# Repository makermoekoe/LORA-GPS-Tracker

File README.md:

# LORA-GPS-Tracker

**This page is a work in progress!**

</a>

This LORA-GPS-Tracker was designed to just test three modules, which I haven't worked with yet: the RFM95 LORA module, the ESP32-S2-Mini module and the ATGM336h GPS module. All combined this device can be used as a GPS-Tracker for LORA based systems. Additionally to the modules, the board includes a 0.96" OLED display, two user buttons, a user RGB LED, a LiPo battery charger with a 16340 cell holder, and a dual LDO setup, which is very handy when it comes to deep sleeping.

Here are some specs of the board:
- ESP32-S2-Mini
- USB Type-C for charging the battery and flashing the ESP32
- Dual LDO setup, which will reduce the sleep current (the main power sinks can be shut down before entering a sleep mode)
- Power friendly OLED display
- Dimensions are 60x43mm

The [Youtube Video](https://youtu.be/C7jFupvuy9M) shows the PCB assembly process, some initial tests and some power measurements.

## Connections

The RFM95 LORA module is connected via SPI, the ATGM336h GPS module is connected via UART and the OLED display is connected via I2C.

GPIO ESP32 | Function | Mode
-------- | -------- | --------
GPIO1 | LORA_RST | Output
GPIO2 | LORA_MISO | Input
GPIO3 | LORA_MOSI | Output
GPIO4 | LORA_SCK | Output
GPIO5 | LORA_CS | Output
GPIO6 | LORA_INT | Input
GPIO7 | LORA_DIO1 | Data
GPIO8 | LORA_DIO2 | Data
GPIO12 | Button2 | Input
GPIO14 | Enable LDO2 | Output
GPIO15 | BAT_ADC | Input
GPIO16 | Button1 | Input
GPIO19 | USB_DN | Data
GPIO20 | USB_DP | Data
GPIO34 | OLED_RST | Output
GPIO35 | I2C_SCL | Output
GPIO36 | I2C_SDA | Data
GPIO37 | LED_CLK | Output
GPIO38 | LED_SDI | Data
GPIO40 | GPS_PPS | Input
GPIO41 | GPS_RXD | Input
GPIO42 | GPS_TXD | Output

By switching off the EN_LDO2 output, the second LDO which powers the GPS as well as LORA module, the onboard LED and the OLED display, will be shut down.

## Power measurements

</a>

State | Avg. current | Peak current
-------- | -------- | --------
Reading sensors | 80mA | 92mA
Transmitting LORA | 135mA | 208mA
Deep sleep | 75µA | 82µA

Note: The schematics in this repo have the I2C pull-up resistors connected to +3V3. It reduces the power consumption if you don't mount these resistors or if you connect them to VDD (controllable via LDO2).

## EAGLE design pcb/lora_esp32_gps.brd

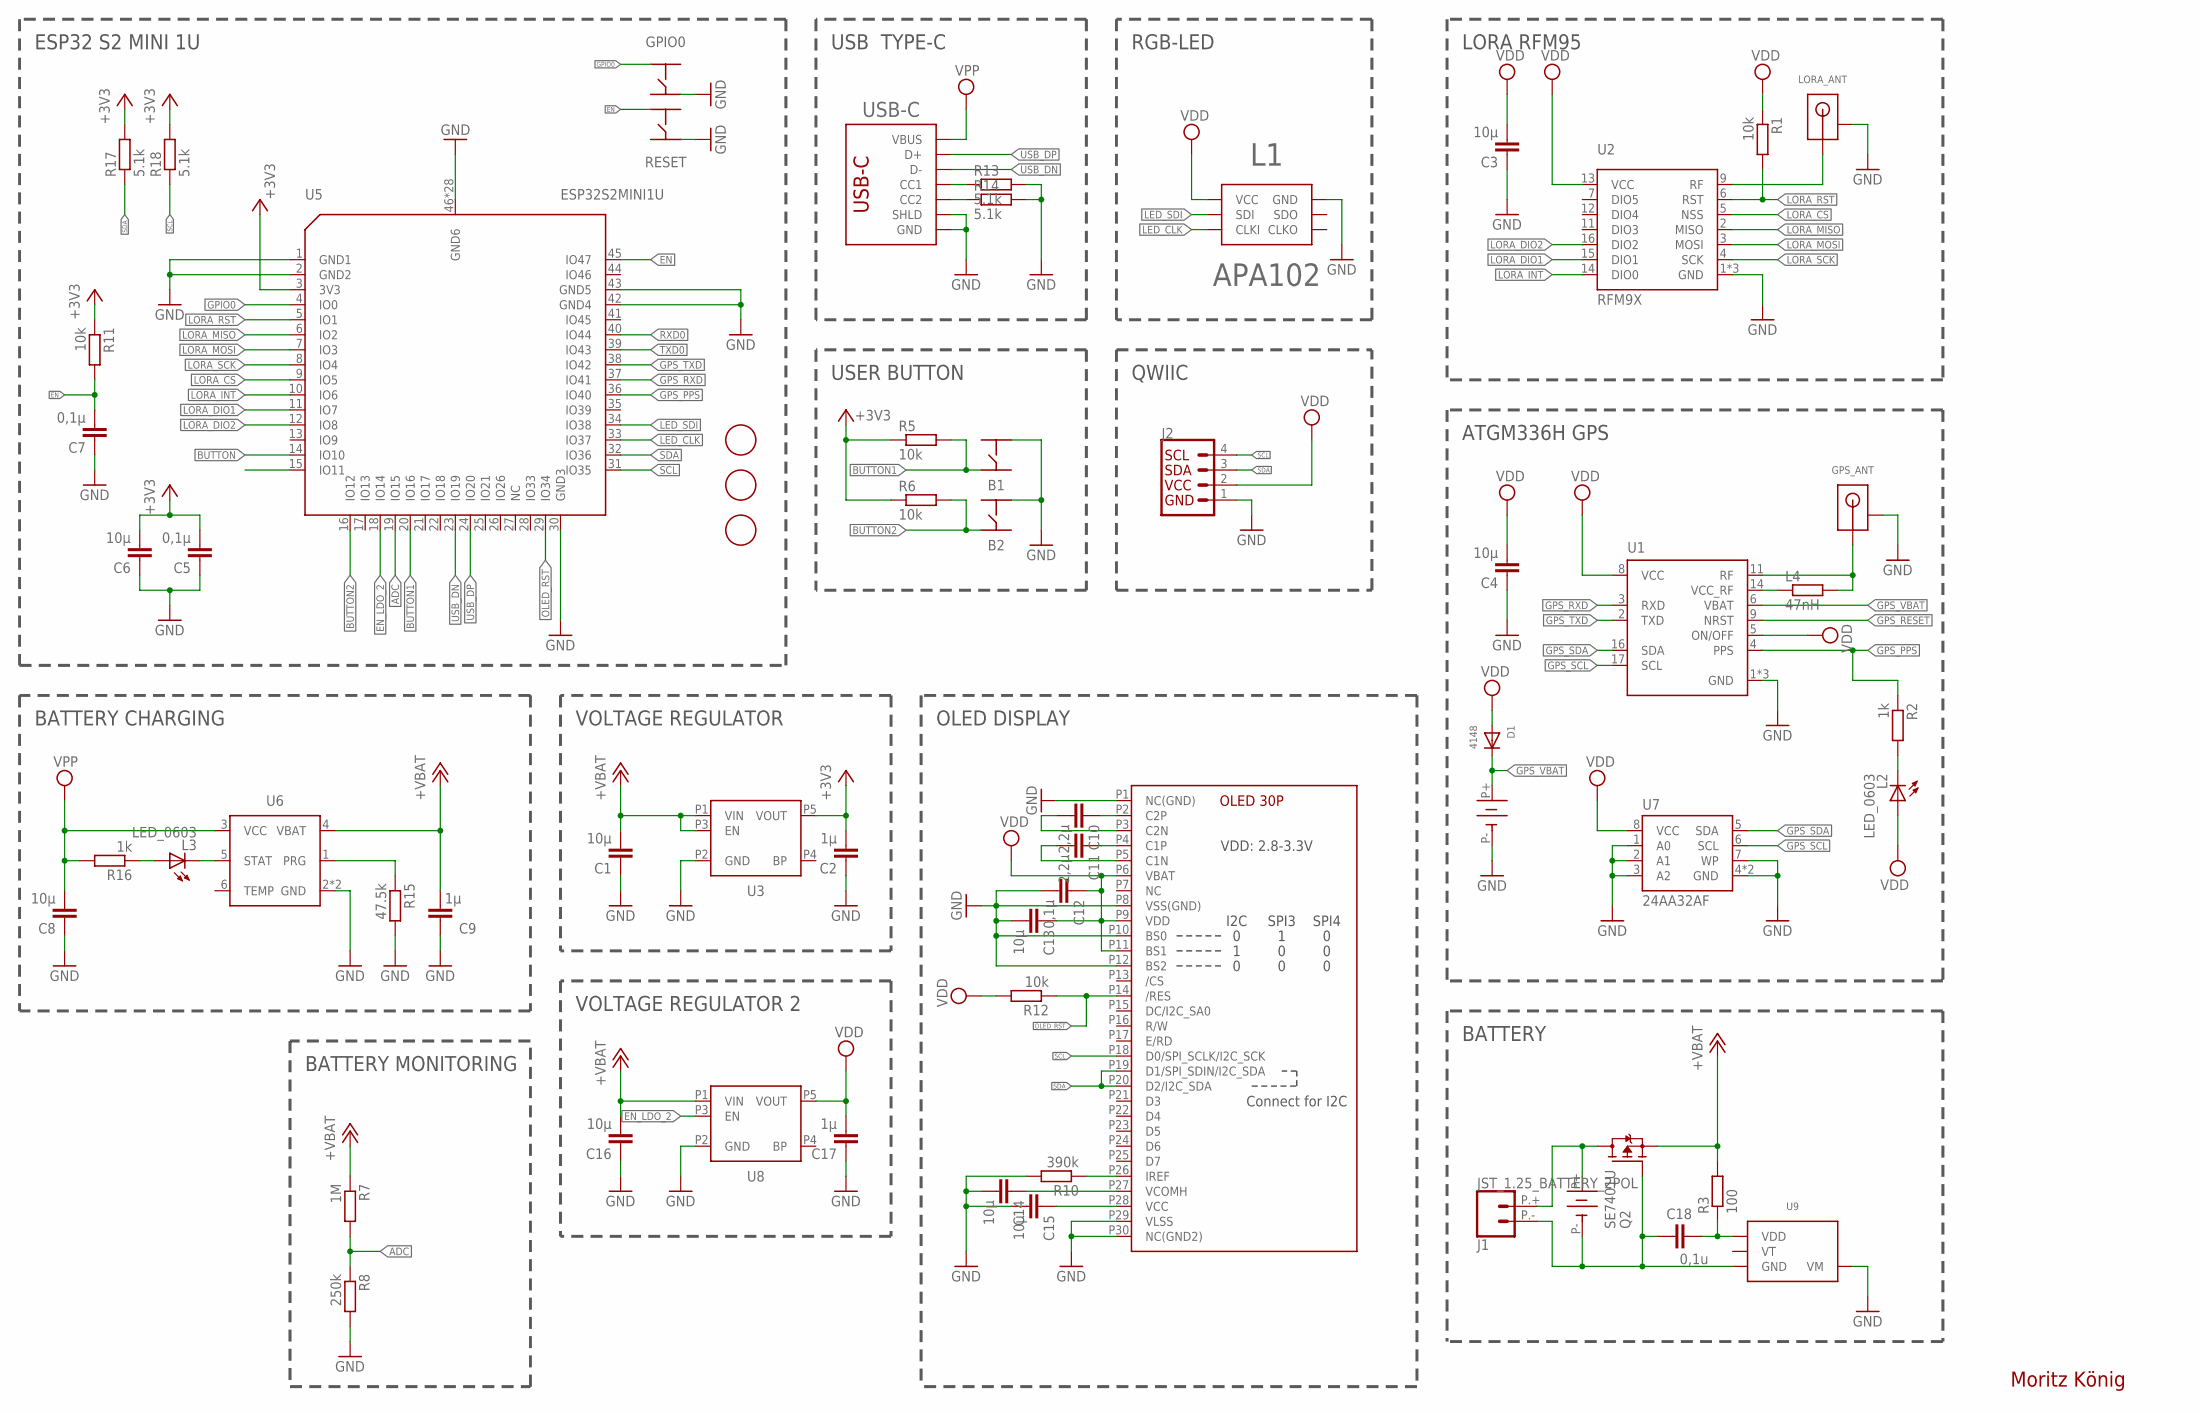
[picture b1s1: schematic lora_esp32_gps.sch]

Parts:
B1, B2: PTS840ESDGMSMTRLFS
BAT2: MS621
C1, C3, C4, C6, C8, C13, C14, C15, C16: 10µ; C0603
C2, C9, C17: 1µ; C0603
C5, C7, C12: 0,1µ; C0603
C10, C11: 2,2µ; C0603
C18: 0,1u; C0603
D1: 4148; SOD-323F
FID1, FID2, FID3: FIDUCIAL; FIDUCIAL_1MM
GPIO0: BUTTON_4PIN_TS_1177; TS-1177-C-B-B
GPS_ANT: UFL_ANT_CONNECTOR
J1: JST_1.25_BATTERY_2POL; JST_1.25MM_2POL
J2: QWIIC_CONNECTORJS-1MM; 1X04_1MM_RA
L1: APA102_2020
L2, L3: LED_0603; CHIPLED_0603
L4: 47nH; R0402
LORA_ANT: UFL_ANT_CONNECTOR
Q2: SE7401U; SOT323
R1, R5, R6, R11, R12: 10k; R0603
R2, R16: 1k; R0603
R3: 100; R0603
R7: 1M; R0603
R8: 250k; R0603
R10: 390k; R0603
R13, R14, R17, R18: 5.1k; R0603
R15: 47.5k; R0603
RESET: BUTTON_4PIN_TS_1177; TS-1177-C-B-B
U1: ATGM336H; ATGM336H-MODULE
U2: RFM9X; LORA_RFM9X
U3, U8: RT9193_SC70-5; SC-70-5
U4: OLD_096_SSD1306_30P_2B; OLED_096_30P_B
U5: ESP32S2MINI1U; ESP32-S2-MINI-1U
U6: WS4518D; DFN-6
U7: 24AA32AF; TDFN8
U9: XB5353A; SOT23-5
U$2: BATTERY_KEYSTONE_1051; KEYSTONE_1051
USB-C: USB_C_C393939; USBC_C393939

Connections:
+3V3: C2.2, C5.2, C6.2, R5.1, R6.1, R11.1, R17.2, R18.2, U3.P5 (VOUT), U5.3 (3V3)
+VBAT: C1.2, C9.2, C16.2, Q2.2 (S), R3.2, R7.1, U3.P1 (VIN), U3.P3 (EN), U6.4 (VBAT), U8.P1 (VIN)
ADC: R7.2, R8.1, U5.19 (IO15)
BUTTON: U5.14 (IO10)
BUTTON1: B1.2, R5.2, U5.20 (IO16)
BUTTON2: B2.2, R6.2, U5.16 (IO12)
EN: C7.2, R11.2, RESET.P4 (4), U5.45 (IO47)
EN_LDO_2: U5.18 (IO14), U8.P3 (EN)
GND: B1.3, B2.3, BAT2.P- (GND), C1.1, C2.1, C3.1, C4.1, C5.1, C6.1, C7.1, C8.1, C9.1, C12.2, C13.2, C14.2, C15.2, C16.1, C17.1, GPIO0.P1 (1), GPS_ANT.P1.- (GND), GPS_ANT.P2.- (GND), J2.1 (GND), L1.P6 (GND), L1.P6.1 (GND), LORA_ANT.P1.- (GND), LORA_ANT.P2.- (GND), R8.2, R10.2, R13.2, R14.2, R15.2, RESET.P1 (1), U1.1 (GND), U1.10 (GND), U1.12 (GND), U2.1 (GND), U2.8 (GND), U2.10 (GND), U3.P2 (GND), U4.P1 (NC(GND)), U4.P8 (VSS(GND)), U4.P10 (BS0), U4.P12 (BS2), U4.P29 (VLSS), U4.P30 (NC(GND2)), U5.1 (GND1), U5.2 (GND2), U5.30 (GND3), U5.42 (GND4), U5.43 (GND5), U5.46 (GND6), U5.47 (GND6), U5.48 (GND6), U5.49 (GND6), U5.50 (GND6), U5.51 (GND6), U5.52 (GND6), U5.53 (GND6), U5.54 (GND6), U5.55 (GND6), U5.56 (GND6), U5.57 (GND6), U5.58 (GND6), U5.59 (GND6), U5.60 (GND6), U5.61 (GND6), U5.62 (GND6), U5.63 (GND6), U5.64 (GND6), U5.65 (GND6), U5.66 (GND6), U5.67 (GND6), U5.68 (GND6), U5.69 (GND6), U5.70 (GND6), U5.71 (GND6), U5.72 (GND6), U5.73 (GND6), U6.2 (GND), U6.EXP (GND), U7.1 (A0), U7.2 (A1), U7.3 (A2), U7.4 (GND), U7.7 (WP), U7.EXP (GND), U8.P2 (GND), U9.4 (VM), U9.5 (VM), USB-C.A1B12 (GND), USB-C.B1A12 (GND), USB-C.S1 (SHLD), USB-C.S2 (SHLD), USB-C.S3 (SHLD), USB-C.S4 (SHLD)
GPIO0: GPIO0.P4 (4), U5.4 (IO0)
GPS_PPS: R2.1, U1.4 (PPS), U5.36 (IO40)
GPS_RESET: U1.9 (NRST)
GPS_RXD: U1.3 (RXD), U5.37 (IO41)
GPS_SCL: U1.17 (SCL), U7.6 (SCL)
GPS_SDA: U1.16 (SDA), U7.5 (SDA)
GPS_TXD: U1.2 (TXD), U5.38 (IO42)
GPS_VBAT: BAT2.P+ (VCC), D1.C, U1.6 (VBAT)
LED_CLK: L1.P5 (CLKI), U5.33 (IO37)
LED_SDI: L1.P4 (SDI), U5.34 (IO38)
LORA_CS: U2.5 (NSS), U5.9 (IO5)
LORA_DIO1: U2.15 (DIO1), U5.11 (IO7)
LORA_DIO2: U2.16 (DIO2), U5.12 (IO8)
LORA_INT: U2.14 (DIO0), U5.10 (IO6)
LORA_MISO: U2.2 (MISO), U5.6 (IO2)
LORA_MOSI: U2.3 (MOSI), U5.7 (IO3)
LORA_RST: R1.2, U2.6 (RST), U5.5 (IO1)
LORA_SCK: U2.4 (SCK), U5.8 (IO4)
unnamed: L4.1, U1.14 (VCC_RF)
unnamed: L2.P$1 (C), R2.2
unnamed: GPS_ANT.ANT, L4.2, U1.11 (RF)
unnamed: LORA_ANT.ANT, U2.9 (RF)
unnamed: C18.2, R3.1, U9.3 (VDD)
unnamed: C18.1, J1.P.- (2), Q2.1 (G), U9.2 (GND), U$2.P- (GND)
unnamed: R15.1, U6.1 (PRG)
unnamed: J1.P.+ (1), Q2.3 (D), U$2.P+ (VCC)
unnamed: R14.1, USB-C.B5 (CC2)
unnamed: C10.1, U4.P2 (C2P)
unnamed: C10.2, U4.P3 (C2N)
unnamed: C11.2, U4.P5 (C1N)
unnamed: R10.1, U4.P26 (IREF)
unnamed: R13.1, USB-C.A5 (CC1)
unnamed: C11.1, U4.P4 (C1P)
unnamed: C15.1, U4.P28 (VCC)
unnamed: C14.1, U4.P27 (VCOMH)
unnamed: L3.P$2 (A), R16.1
unnamed: L3.P$1 (C), U6.5 (STAT)
OLED_RST: R12.1, U4.P14 (/RES), U5.29 (IO34)
RXD0: U5.40 (IO44)
SCL: J2.4 (SCL), R18.1, U4.P18 (D0/SPI_SCLK/I2C_SCK), U5.31 (IO35)
SDA: J2.3 (SDA), R17.1, U4.P19 (D1/SPI_SDIN/I2C_SDA), U4.P20 (D2/I2C_SDA), U5.32 (IO36)
TXD0: U5.39 (IO43)
USB_DN: U5.23 (IO19), USB-C.A7 (D-), USB-C.B7 (D-)
USB_DP: U5.24 (IO20), USB-C.A6 (D+), USB-C.B6 (D+)
VDD: C3.2, C4.2, C12.1, C13.1, C17.2, D1.A, J2.2 (VCC), L1.P1 (VCC), L1.P1.1 (VCC), L2.P$2 (A), R1.1, R12.2, U1.5 (ON/OFF), U1.8 (VCC), U2.13 (VCC), U4.P6 (VBAT), U4.P9 (VDD), U4.P11 (BS1), U7.8 (VCC), U8.P5 (VOUT)
VPP: C8.2, R16.2, U6.3 (VCC), USB-C.A4B9 (VBUS), USB-C.B4A9 (VBUS)

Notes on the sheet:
Moritz König
BATTERY MONITORING
USB TYPE-C
VOLTAGE REGULATOR
RGB-LED
BATTERY CHARGING
BATTERY
USER BUTTON
OLED DISPLAY
QWIIC
ESP32 S2 MINI 1U
LORA RFM95
ATGM336H GPS
VOLTAGE REGULATOR 2

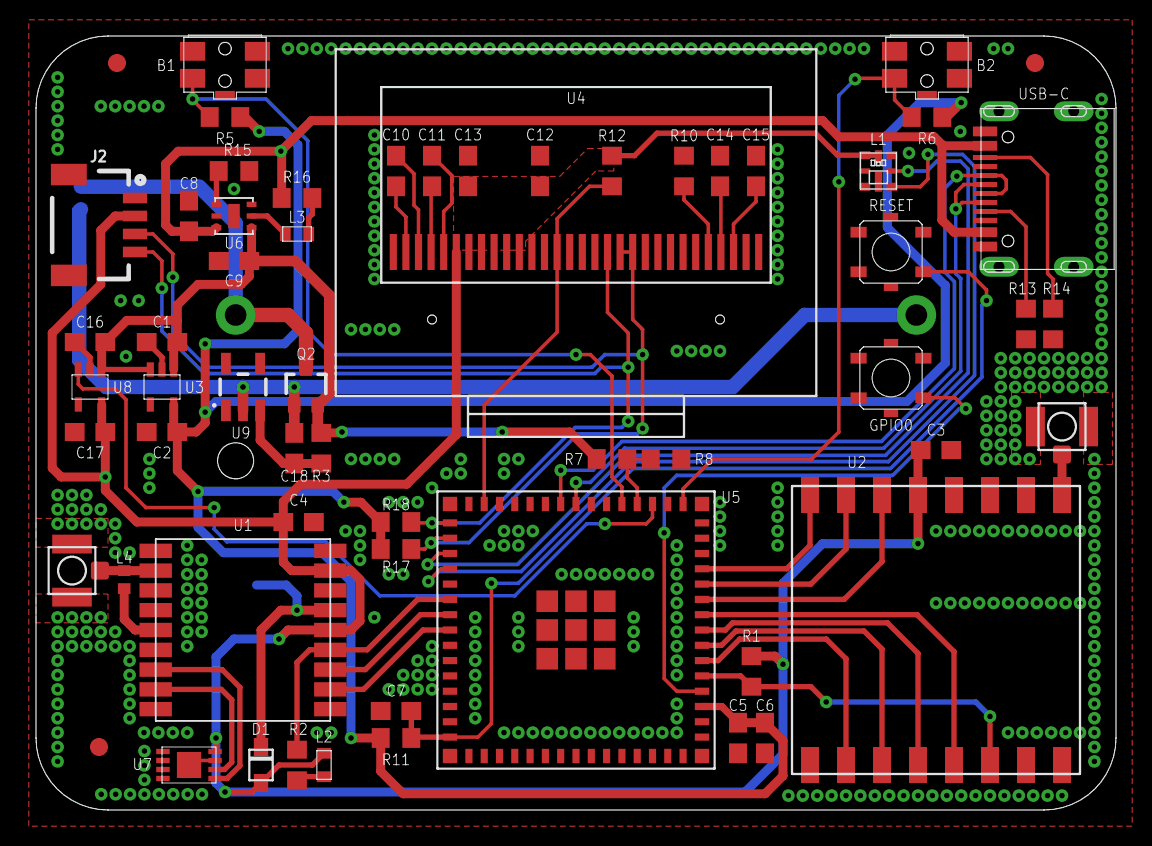
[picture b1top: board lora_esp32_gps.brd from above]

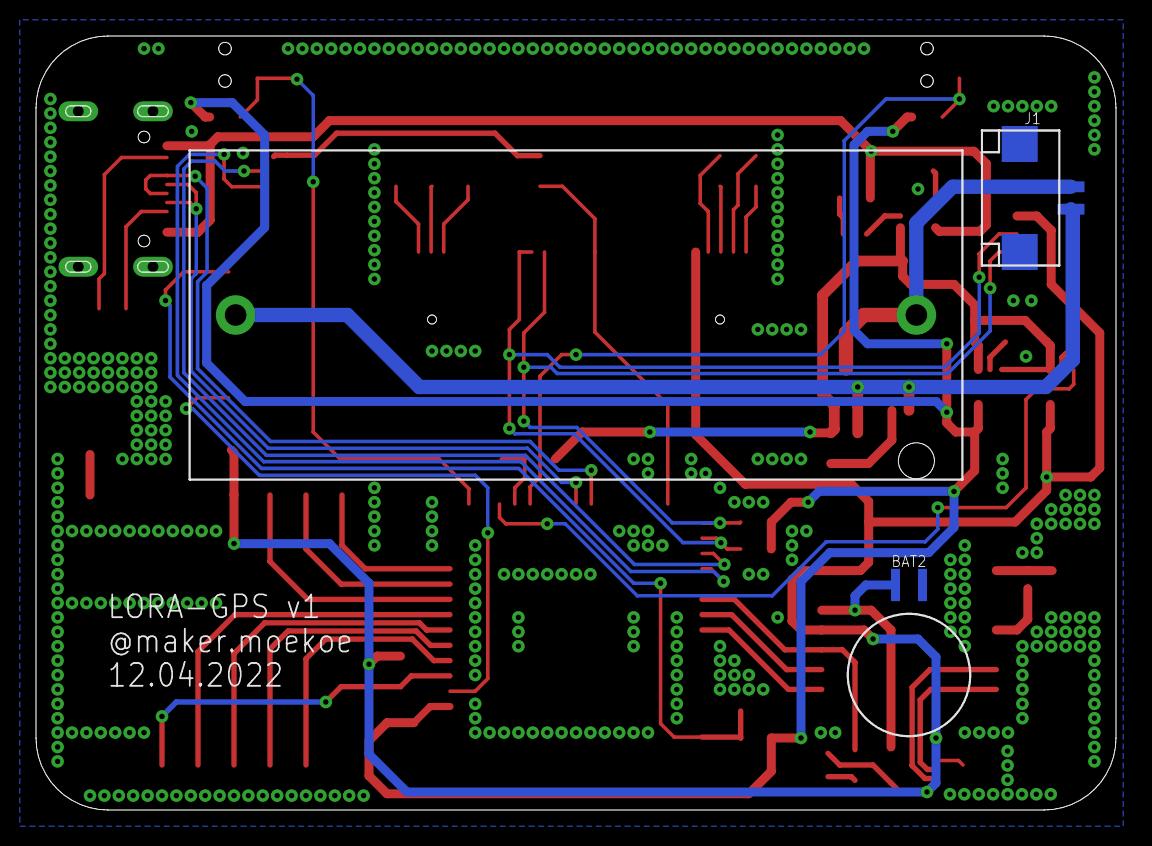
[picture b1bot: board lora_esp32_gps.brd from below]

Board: 2 copper layers, 60.0 x 43.0 mm, 63 parts (3 on the bottom side), 51 nets.

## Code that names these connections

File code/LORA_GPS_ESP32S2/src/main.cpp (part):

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#define BTN2_PIN        12
#define EN_LDO2_PIN     14
#define ADC_PIN         15
#define OLED_RST_PIN    34

#define LORA_RST_PIN    1
#define LORA_MISO_PIN   2
#define LORA_MOSI_PIN   3
#define LORA_SCK_PIN    4
#define LORA_CS_PIN     5
#define LORA_INT_PIN    6
#define LORA_DIO1_PIN   7
#define LORA_DIO2_PIN   8

#define SDA_PIN_M       36
#define SCL_PIN_M       35

#define GPS_PPS_PIN     40
#define GPS_RXD_PIN     42
#define GPS_TXD_PIN     41


#define NUM_LEDS        1
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
#define WIDTH 128
#define HEIGHT 64
U8G2_SSD1306_128X64_NONAME_F_HW_I2C u8g2(U8G2_R0, /* reset=*/ OLED_RST_PIN, /* clock=*/ SCL_PIN_M, /* data=*/ SDA_PIN_M);

const char* ssid = "XXX";
const char* password = "XXX";
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
void setup() {
  Serial.begin(115200);
  Serial1.begin(9600, SERIAL_8N1, GPS_RXD_PIN, GPS_TXD_PIN, false);

  pinMode(EN_LDO2_PIN, OUTPUT);
  digitalWrite(EN_LDO2_PIN, HIGH);

  pinMode(GPS_PPS_PIN, INPUT);
  pinMode(BTN1_PIN, INPUT);
  pinMode(BTN2_PIN, INPUT);
  pinMode(ADC_PIN, INPUT);
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  leds[0] = CRGB::Green;
  FastLED.show();

  SPI.begin(LORA_SCK_PIN, LORA_MISO_PIN, LORA_MOSI_PIN, LORA_CS_PIN);
  LoRa.setPins(LORA_CS_PIN, LORA_RST_PIN, LORA_DIO1_PIN);

  if (!LoRa.begin(866E6)) {
    Serial.println("LoRa fail!");
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     }
  }

  if(digitalRead(GPS_PPS_PIN) == 1 && gps_pps_state){
    gps_pps_delay = millis() - gps_last_pps_signal;
    gps_last_pps_signal = millis();
    String pps_str = "PPS delay: " + String(gps_pps_delay);
    Serial.println(pps_str);
    gps_pps_state = false;
  }
  else if(digitalRead(GPS_PPS_PIN) == 0 && !gps_pps_state){
    gps_pps_state = true;
  }

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
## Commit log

2022-05-20 initial commit with PCB and test code
2022-06-30 added pinout table
2022-07-04 added description and power measurements
2022-07-04 added deepsleep and gateway code
2022-07-04 added schematics

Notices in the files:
parts and their libraries:
SparkFun-Connectors: Licensing: Creative Commons ShareAlike 4.0 International - https://creativecommons.org/licenses/by-sa/4.0
